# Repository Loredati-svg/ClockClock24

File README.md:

# ClockClock 24 – Replica v2

A personal re-implementation of the **ClockClock 24** kinetic sculpture by [Humans Since 1982](https://www.humanssince1982.com/): 24 analog clocks in a 3 × 8 grid whose hands move together to show the time in digital form.

Inspired by [Vallasc/clockclock24-replica](https://github.com/Vallasc/clockclock24-replica), with a redesigned architecture: ESP32-S3 controllers, USB-C on every board, an auto-addressed I2C bus and separate motor boards.

> For personal, non-commercial use only. All design rights belong to Humans Since 1982.

<p align="center"><em>Controller board, rev A (3D render, top and bottom)</em></p>

## Architecture

**6 identical controller boards** (2 per row), each driving **4 clocks (8 motors)** via cables to **24 passive motor boards**, one behind each clock.

- Same hardware and firmware on every controller.
- The **first board in the chain** becomes the **master**: WiFi, NTP, web interface, and it sends target positions to the others over I2C.
- Each controller generates step pulses for its own motors, so only short, slow messages travel on the bus.

### Controller board – rev A (layout in review)

USB-C (5 V, programming + debug via native USB) → protection → +5 V rail → 2× VID6606 drivers and the bus; AP7361C LDO → 3.3 V for the ESP32-S3-WROOM-1-N8.

### Motor board – in development

A minimal board with only the motor and its connector: one VID28-05 / BKA30D-R5 dual-shaft stepper (two motors, coaxial shafts, one hand each) and one 8-pin connector. No active parts.

Public documentation on this motor is scarce (mechanical drawings, pin numbering and the 360° no-stop variant all differ between sellers), so the footprint and pinout are being validated on real samples before the board is finalized.

## Bus and master detection

The bus connectors carry `+5V`, `GND`, `I2C_SDA` (IO41), `I2C_SCL` (IO42) and a `CHAIN` line.

- Nothing on `BUS_IN` → `CHAIN_IN` high → **master**. Cable present → low → **slave**, even if the upstream board is still booting.
- At startup the master passes a "token" down the chain via `CHAIN_OUT`. Each board answers on a temporary I2C address and receives its permanent one, so addresses match the physical order automatically.
- I2C pull-ups (4.7 kΩ) are on every board but enabled only via solder jumpers **JP1 / JP2: close them on the master only**.

## Connectors

**Bus – `BUS_IN` / `BUS_OUT`** (JST-XH 8 pin, straight cables)

| 1 | 2 | 3 | 4 | 5 | 6 | 7 | 8 |
|---|---|---|---|---|---|---|---|
| +5V | +5V | GND | GND | SDA | SCL | CHAIN_IN / OUT | GND |

**Motors – `CLK1`…`CLK4`** (JST-PH 8 pin): pins 1–4 = first motor (`OUT1–4`), pins 5–8 = second motor. Same pinout on every connector and motor board, so all cables and motor boards are interchangeable. Using different connector families for bus and motors makes it impossible to plug a bus cable into a motor output.

## Good to know

- **Motors**: use the **360° version without end stops** of the VID28-05 / BKA30D-R5. It's hard to find, so order samples first.
- **Resolution**: 1/12° per step → 4320 steps per revolution, max ~7.2 kHz step rate (600°/s).
- **No position sensors**: hand positions are saved in flash after every move. A "moving" flag detects power loss mid-movement, and calibration (±1 step per hand) is done from the web interface.
- **Backlash** (~0.5–1°): always do the final approach from the same direction.
- **Idle coils off**: `VID_RST` is pulled low after each move. The 180:1 gearbox holds the hands, which saves power and heat.
- **Power**: realistically < 2 A for the whole clock with all hands moving. Any board can be the 5 V entry point (USB-C max 3 A).
- **VID6606 logic level**: VIH min is 3.15 V at 5 V supply, so 3.3 V from the ESP32 works but with little margin. Not available at LCSC: hand-solder (SOP-28).
- **PCB**: 4 layers (signals / GND / +5V / signals), KiCad 10. The ESP32-S3 library footprint's keep-out can trigger false DRC errors in KiCad 10: replace it with a board-level rule area.
- **Firmware**: PlatformIO, `-DARDUINO_USB_CDC_ON_BOOT=1` (TXD0 is used for the status LED).

## Credits

- Original design: [Humans Since 1982](https://www.humanssince1982.com/)
- Reference replica: [Vallasc/clockclock24-replica](https://github.com/Vallasc/clockclock24-replica)
- Hardware v2: Lorenzo Dati

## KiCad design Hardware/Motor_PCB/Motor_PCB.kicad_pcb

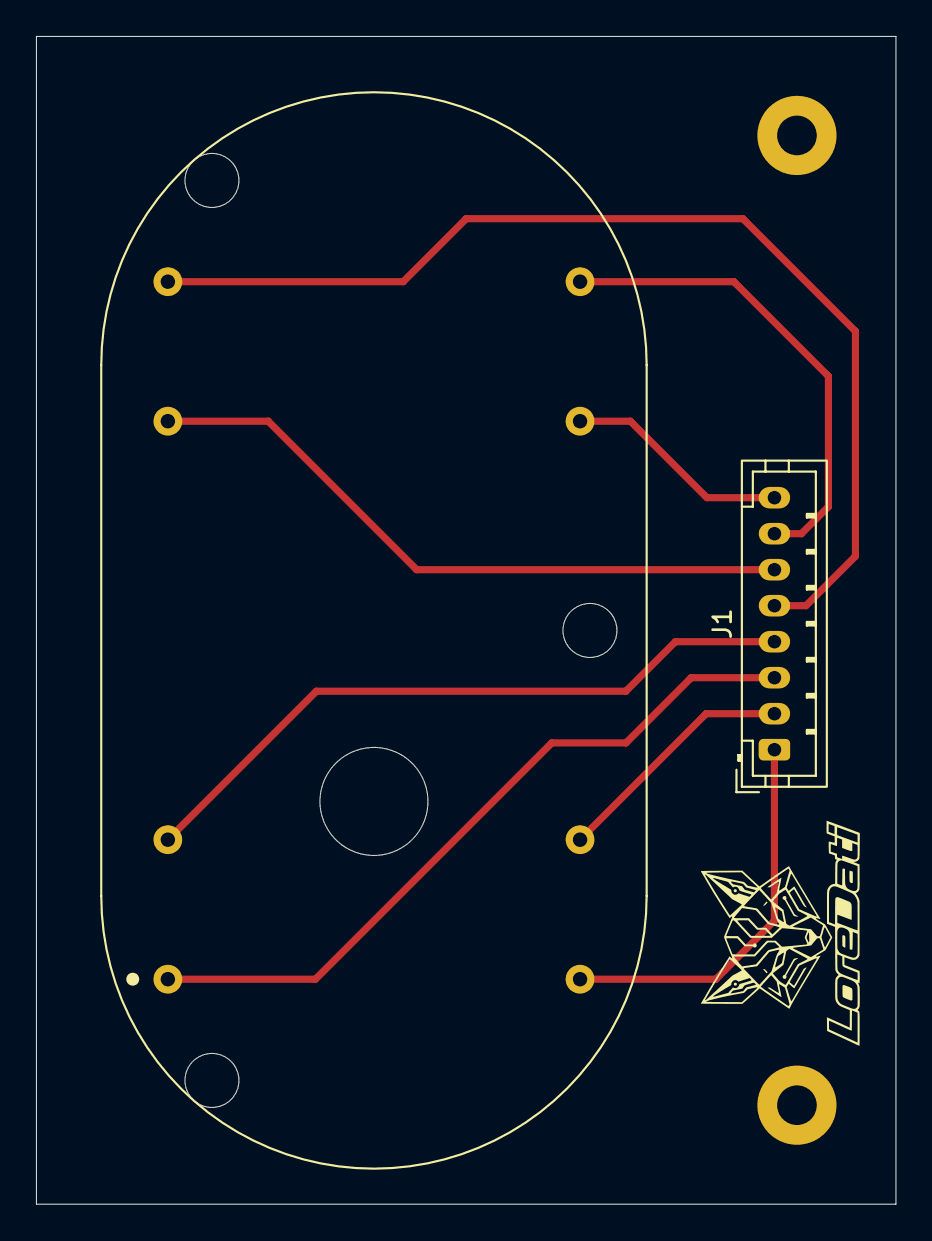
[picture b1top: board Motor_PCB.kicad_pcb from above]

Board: 2 copper layers, 47.8 x 64.9 mm, 4 parts (0 on the bottom side), 8 nets.

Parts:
H1, H2: MountingHole; MountingHole_2.2mm_M2_Pad
J1: Conn_01x08; JST_PH_B8B-PH-K_1x08_P2.00mm_Vertical
M1: BKA30D-R5

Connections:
/M1_1: J1.4, M1.1 (M1_A+)
/M1_2: J1.3, M1.2 (M1_A-)
/M1_3: J1.1, M1.3 (M1_B+)
/M1_4: J1.2, M1.4 (M1_B-)
/M2_1: J1.8, M1.5 (M2_A+)
/M2_2: J1.7, M1.6 (M2_A-)
/M2_3: J1.5, M1.7 (M2_B+)
/M2_4: J1.6, M1.8 (M2_B-)

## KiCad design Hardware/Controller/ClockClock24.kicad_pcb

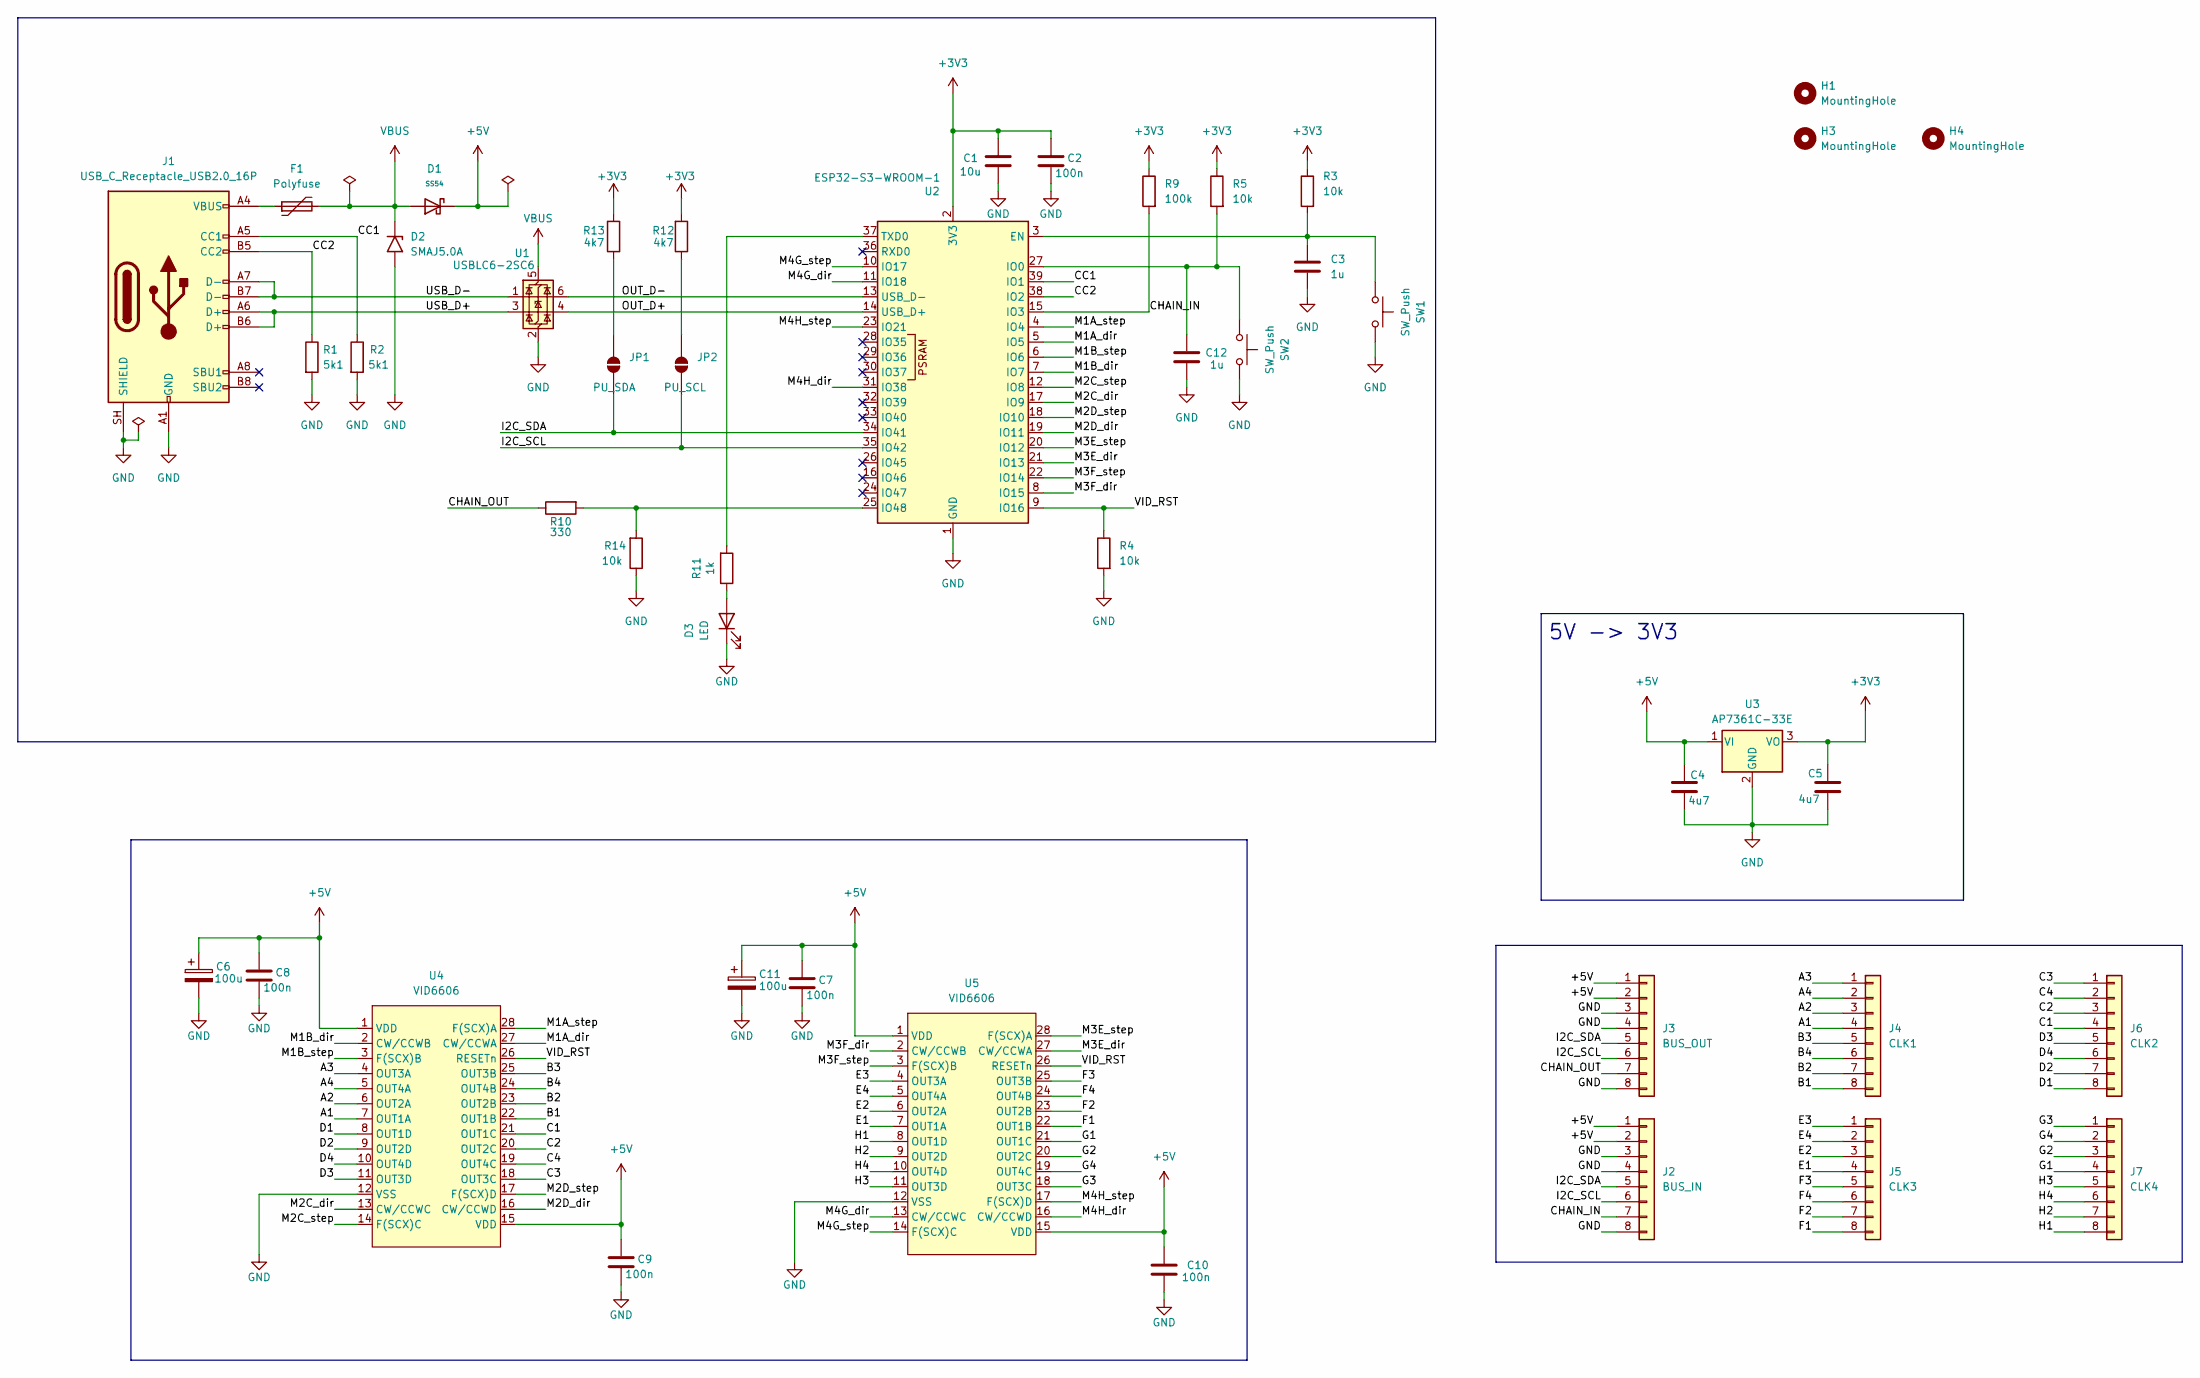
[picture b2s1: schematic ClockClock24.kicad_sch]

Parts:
C1: 10u; 0603; LCSC C19702
C2, C7, C8, C9, C10: 100n; 0603; LCSC C66501
C3, C12: 1u; 0603; LCSC C1592
C4, C5: 4u7; 0603; LCSC C19666
C6, C11: 100u; CP_Elec_6.3x5.4; LCSC C7469933
D1: SS54; D_SMA; Forward Voltage (Vf@If) 550mV@5A; Reverse Voltage (Vr) 40V; Part SS54; LCSC C22452
D2: SMAJ5.0A; D_SMA; LCSC C113952
D3: LED; 0603_pol; LCSC C22371297
F1: Polyfuse; Fuse_1206_3216Metric; LCSC C269119
H1, H3, H4: MountingHole; MountingHole_2.2mm_M2_Pad
J1: USB_C_Receptacle_USB2.0_16P; USB_C_Receptacle_HRO_TYPE-C-31-M-12; LCSC C165948
J2: BUS_IN; JST_XH_B8B-XH-A_1x08_P2.50mm_Vertical; LCSC C157972
J3: BUS_OUT; JST_XH_B8B-XH-A_1x08_P2.50mm_Vertical; LCSC C157972
J4: CLK1; JST_PH_B8B-PH-K_1x08_P2.00mm_Vertical; LCSC C157974
J5: CLK3; JST_PH_B8B-PH-K_1x08_P2.00mm_Vertical; LCSC C157974
J6: CLK2; JST_PH_B8B-PH-K_1x08_P2.00mm_Vertical; LCSC C157974
J7: CLK4; JST_PH_B8B-PH-K_1x08_P2.00mm_Vertical; LCSC C157974
JP1: PU_SDA; SolderJumper-2_P1.3mm_Open_RoundedPad1.0x1.5mm
JP2: PU_SCL; SolderJumper-2_P1.3mm_Open_RoundedPad1.0x1.5mm
R1, R2: 5k1; 0603; LCSC C23186
R3, R4, R5, R14: 10k; 0603; LCSC C98220
R9: 100k; 0603; LCSC C14675
R10: 330; 0603; LCSC C105881
R11: 1k; 0603; LCSC C22548
R12, R13: 4k7; 0603; LCSC C99782
SW1, SW2: SW_Push; SW_SPST_B3U-1000P; LCSC C231329
U1: USBLC6-2SC6; SOT-23-6; LCSC C7519
U2: ESP32-S3-WROOM-1; LCSC C2913198
U3: AP7361C-33E; SOT-223-3_TabPin2; LCSC C500795
U4, U5: VID6606; SOIC-28W_7.5x17.9mm_P1.27mm

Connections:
+3V3: C1.1, C2.1, C5.1, R3.1, R5.1, R9.1, R12.2, R13.2, U2.2 (3V3), U3.3 (VO)
+5V: C4.1, C6.1, C7.1, C8.1, C9.1, C10.1, C11.1, D1.1, J2.1, J2.2, J3.1, J3.2, U3.1 (VI), U4.1 (VDD), U4.15 (VDD), U5.1 (VDD), U5.15 (VDD)
/A1: J4.4, U4.7 (OUT1A)
/A2: J4.3, U4.6 (OUT2A)
/A3: J4.1, U4.4 (OUT3A)
/A4: J4.2, U4.5 (OUT4A)
/B1: J4.8, U4.22 (OUT1B)
/B2: J4.7, U4.23 (OUT2B)
/B3: J4.5, U4.25 (OUT3B)
/B4: J4.6, U4.24 (OUT4B)
/C1: J6.4, U4.21 (OUT1C)
/C2: J6.3, U4.20 (OUT2C)
/C3: J6.1, U4.18 (OUT3C)
/C4: J6.2, U4.19 (OUT4C)
/CC1: J1.A5 (CC1), R2.1, U2.39 (IO1)
/CC2: J1.B5 (CC2), R1.1, U2.38 (IO2)
/CHAIN_IN: J2.7, R9.2, U2.15 (IO3)
/CHAIN_OUT: J3.7, R10.1
/D1: J6.8, U4.8 (OUT1D)
/D2: J6.7, U4.9 (OUT2D)
/D3: J6.5, U4.11 (OUT3D)
/D4: J6.6, U4.10 (OUT4D)
/E1: J5.4, U5.7 (OUT1A)
/E2: J5.3, U5.6 (OUT2A)
/E3: J5.1, U5.4 (OUT3A)
/E4: J5.2, U5.5 (OUT4A)
/F1: J5.8, U5.22 (OUT1B)
/F2: J5.7, U5.23 (OUT2B)
/F3: J5.5, U5.25 (OUT3B)
/F4: J5.6, U5.24 (OUT4B)
/G1: J7.4, U5.21 (OUT1C)
/G2: J7.3, U5.20 (OUT2C)
/G3: J7.1, U5.18 (OUT3C)
/G4: J7.2, U5.19 (OUT4C)
/H1: J7.8, U5.8 (OUT1D)
/H2: J7.7, U5.9 (OUT2D)
/H3: J7.5, U5.11 (OUT3D)
/H4: J7.6, U5.10 (OUT4D)
/I2C_SCL: J2.6, J3.6, JP2.1 (A), U2.35 (IO42)
/I2C_SDA: J2.5, J3.5, JP1.1 (A), U2.34 (IO41)
/M1A_dir: U2.5 (IO5), U4.27 (CW/CCWA)
/M1A_step: U2.4 (IO4), U4.28 (F(SCX)A)
/M1B_dir: U2.7 (IO7), U4.2 (CW/CCWB)
/M1B_step: U2.6 (IO6), U4.3 (F(SCX)B)
/M2C_dir: U2.17 (IO9), U4.13 (CW/CCWC)
/M2C_step: U2.12 (IO8), U4.14 (F(SCX)C)
/M2D_dir: U2.19 (IO11), U4.16 (CW/CCWD)
/M2D_step: U2.18 (IO10), U4.17 (F(SCX)D)
/M3E_dir: U2.21 (IO13), U5.27 (CW/CCWA)
/M3E_step: U2.20 (IO12), U5.28 (F(SCX)A)
/M3F_dir: U2.8 (IO15), U5.2 (CW/CCWB)
/M3F_step: U2.22 (IO14), U5.3 (F(SCX)B)
/M4G_dir: U2.11 (IO18), U5.13 (CW/CCWC)
/M4G_step: U2.10 (IO17), U5.14 (F(SCX)C)
/M4H_dir: U2.31 (IO38), U5.16 (CW/CCWD)
/M4H_step: U2.23 (IO21), U5.17 (F(SCX)D)
/OUT_D+: U1.4 (I/O2), U2.14 (USB_D+)
/OUT_D-: U1.6 (I/O1), U2.13 (USB_D-)
/USB_D+: J1.A6 (D+), J1.B6 (D+), U1.3 (I/O2)
/USB_D-: J1.A7 (D-), J1.B7 (D-), U1.1 (I/O1)
/VID_RST: R4.1, U2.9 (IO16), U4.26 (RESETn), U5.26 (RESETn)
GND: C1.2, C2.2, C3.2, C4.2, C5.2, C6.2, C7.2, C8.2, C9.2, C10.2, C11.2, C12.2, D2.2 (A2), D3.1 (K), J1.A1 (GND), J1.A12 (GND), J1.B1 (GND), J1.B12 (GND), J1.SH (SHIELD), J2.3, J2.4, J2.8, J3.3, J3.4, J3.8, R1.2, R2.2, R4.2, R14.1, SW1.2, SW2.2, U1.2 (GND), U2.1 (GND), U2.40 (GND), U2.41 (GND), U3.2 (GND), U4.12 (VSS), U5.12 (VSS)
unnamed: D3.2 (A), R11.1
unnamed: F1.1, J1.A4 (VBUS), J1.A9 (VBUS), J1.B4 (VBUS), J1.B9 (VBUS)
unnamed: JP1.2 (B), R13.1
unnamed: JP2.2 (B), R12.1
unnamed: C3.1, R3.2, SW1.1, U2.3 (EN)
unnamed: C12.1, R5.2, SW2.1, U2.27 (IO0)
unnamed: R10.2, R14.2, U2.25 (IO48)
unnamed: R11.2, U2.37 (TXD0)
VBUS: D1.2, D2.1 (A1), F1.2, U1.5 (VBUS)

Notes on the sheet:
5V -> 3V3

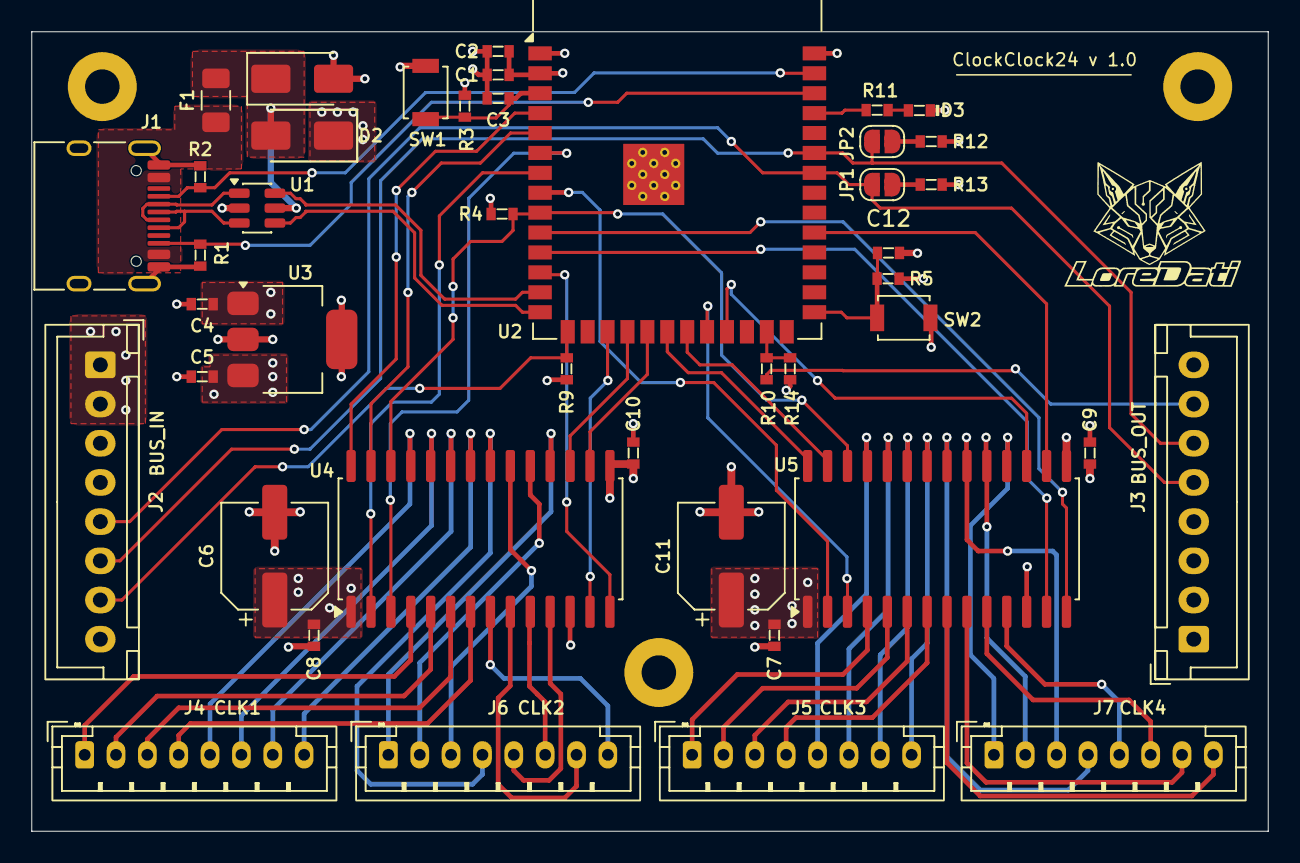
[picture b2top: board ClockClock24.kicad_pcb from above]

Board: 4 copper layers, 78.9 x 51.0 mm, 46 parts (0 on the bottom side), 71 nets.
